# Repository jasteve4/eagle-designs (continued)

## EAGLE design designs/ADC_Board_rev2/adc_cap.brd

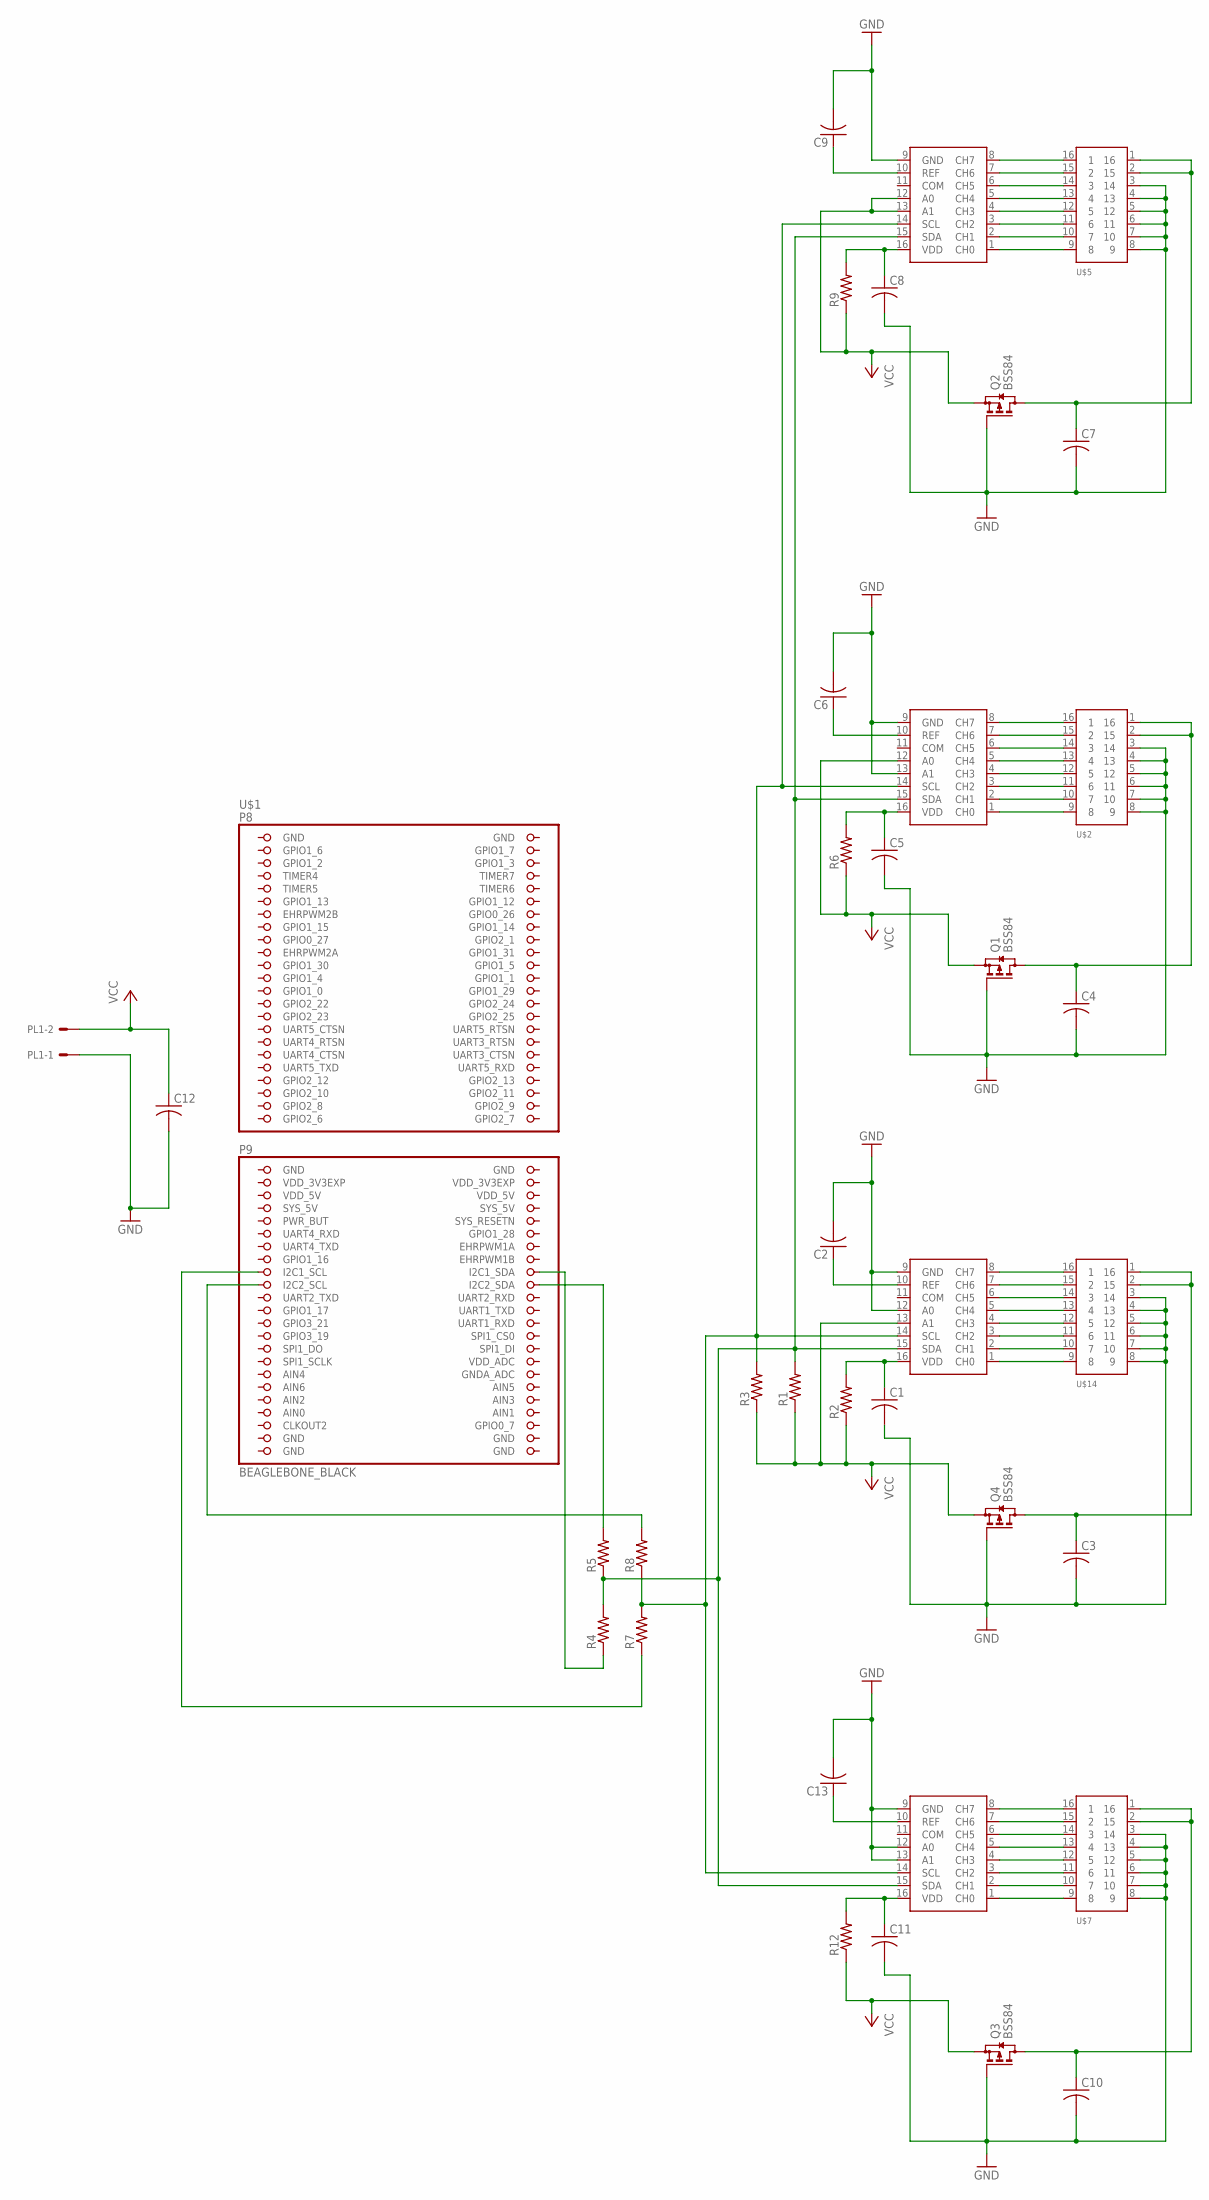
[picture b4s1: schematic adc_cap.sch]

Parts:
C1, C2, C3, C4, C5, C6, C7, C8, C9, C10, C11, C12, C13: C-USC0805; C0805
PL1: 555X-2H; 5569-2
Q1, Q2, Q3, Q4: BSS84; SOT23
R1, R2, R3, R4, R5, R6, R7, R8, R9, R12: R-US_R0805; R0805
U$1: BEAGLEBONE_BLACK; BEAGEBONE
U$2, U$5, U$7, U$14: 2_X_8_CON; 2_X_8_PIN
U$3, U$4, U$6, U$8: ADS7830; ADC8_SD

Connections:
AIN0: U$1.146 (AIN0)
GND: C1.2, C2.2, C3.2, C4.2, C5.2, C6.2, C7.2, C8.2, C9.2, C10.2, C11.2, C12.2, C13.2, PL1.1, Q1.1 (G), Q2.1 (G), Q3.1 (G), Q4.1 (G), U$1.137 (GND), U$1.138 (GND), U$1.139 (GND), U$1.140 (GND), U$1.141 (GND), U$1.142 (GND), U$1.183 (GND), U$1.184 (GND), U$2.3 (14), U$2.4 (13), U$2.5 (12), U$2.6 (11), U$2.7 (10), U$2.8 (9), U$3.9 (GND), U$3.12 (A0), U$4.9 (GND), U$4.13 (A1), U$5.3 (14), U$5.4 (13), U$5.5 (12), U$5.6 (11), U$5.7 (10), U$5.8 (9), U$6.9 (GND), U$7.3 (14), U$7.4 (13), U$7.5 (12), U$7.6 (11), U$7.7 (10), U$7.8 (9), U$8.9 (GND), U$8.12 (A0), U$8.13 (A1), U$14.3 (14), U$14.4 (13), U$14.5 (12), U$14.6 (11), U$14.7 (10), U$14.8 (9)
unnamed: U$3.1 (CH0), U$14.9 (8)
unnamed: R1.2, R4.2, R5.1, U$3.15 (SDA), U$4.15 (SDA), U$6.15 (SDA), U$8.15 (SDA)
unnamed: U$3.2 (CH1), U$14.10 (7)
unnamed: U$3.3 (CH2), U$14.11 (6)
unnamed: U$3.4 (CH3), U$14.12 (5)
unnamed: U$3.5 (CH4), U$14.13 (4)
unnamed: U$3.6 (CH5), U$14.14 (3)
unnamed: U$3.7 (CH6), U$14.15 (2)
unnamed: U$3.8 (CH7), U$14.16 (1)
unnamed: R5.2, U$1.167 (I2C2_SDA)
unnamed: C1.1, R2.2, U$3.16 (VDD)
unnamed: C2.1, U$3.10 (REF)
unnamed: R3.2, R7.2, R8.1, U$3.14 (SCL), U$4.14 (SCL), U$6.14 (SCL), U$8.14 (SCL)
unnamed: C4.1, Q1.3 (D), U$2.1 (16), U$2.2 (15)
unnamed: U$2.9 (8), U$4.1 (CH0)
unnamed: U$2.10 (7), U$4.2 (CH1)
unnamed: U$2.11 (6), U$4.3 (CH2)
unnamed: U$2.12 (5), U$4.4 (CH3)
unnamed: U$2.13 (4), U$4.5 (CH4)
unnamed: U$2.14 (3), U$4.6 (CH5)
unnamed: U$2.15 (2), U$4.7 (CH6)
unnamed: U$2.16 (1), U$4.8 (CH7)
unnamed: R4.1, U$1.165 (I2C1_SDA)
unnamed: R8.2, U$1.166 (I2C2_SCL)
unnamed: C5.1, R6.2, U$4.16 (VDD)
unnamed: C6.1, U$4.10 (REF)
unnamed: C7.1, Q2.3 (D), U$5.1 (16), U$5.2 (15)
unnamed: U$5.9 (8), U$6.1 (CH0)
unnamed: U$5.10 (7), U$6.2 (CH1)
unnamed: U$5.11 (6), U$6.3 (CH2)
unnamed: U$5.12 (5), U$6.4 (CH3)
unnamed: U$5.13 (4), U$6.5 (CH4)
unnamed: U$5.14 (3), U$6.6 (CH5)
unnamed: U$5.15 (2), U$6.7 (CH6)
unnamed: U$5.16 (1), U$6.8 (CH7)
unnamed: R7.1, U$1.168 (I2C1_SCL)
unnamed: C8.1, R9.2, U$6.16 (VDD)
unnamed: C9.1, U$6.10 (REF)
unnamed: C10.1, Q3.3 (D), U$7.1 (16), U$7.2 (15)
unnamed: U$7.9 (8), U$8.1 (CH0)
unnamed: U$7.10 (7), U$8.2 (CH1)
unnamed: U$7.11 (6), U$8.3 (CH2)
unnamed: U$7.12 (5), U$8.4 (CH3)
unnamed: U$7.13 (4), U$8.5 (CH4)
unnamed: U$7.14 (3), U$8.6 (CH5)
unnamed: U$7.15 (2), U$8.7 (CH6)
unnamed: U$7.16 (1), U$8.8 (CH7)
unnamed: C11.1, R12.2, U$8.16 (VDD)
unnamed: C13.1, U$8.10 (REF)
unnamed: C3.1, Q4.3 (D), U$14.1 (16), U$14.2 (15)
SYS_5V: U$1.178 (SYS_5V)
VCC: C12.1, PL1.2, Q1.2 (S), Q2.2 (S), Q3.2 (S), Q4.2 (S), R1.1, R2.1, R3.1, R6.1, R9.1, R12.1, U$3.13 (A1), U$4.12 (A0), U$6.12 (A0), U$6.13 (A1)
VDD_3V3EXP: U$1.181 (VDD_3V3EXP), U$1.182 (VDD_3V3EXP)
VDD_5V: U$1.179 (VDD_5V), U$1.180 (VDD_5V)

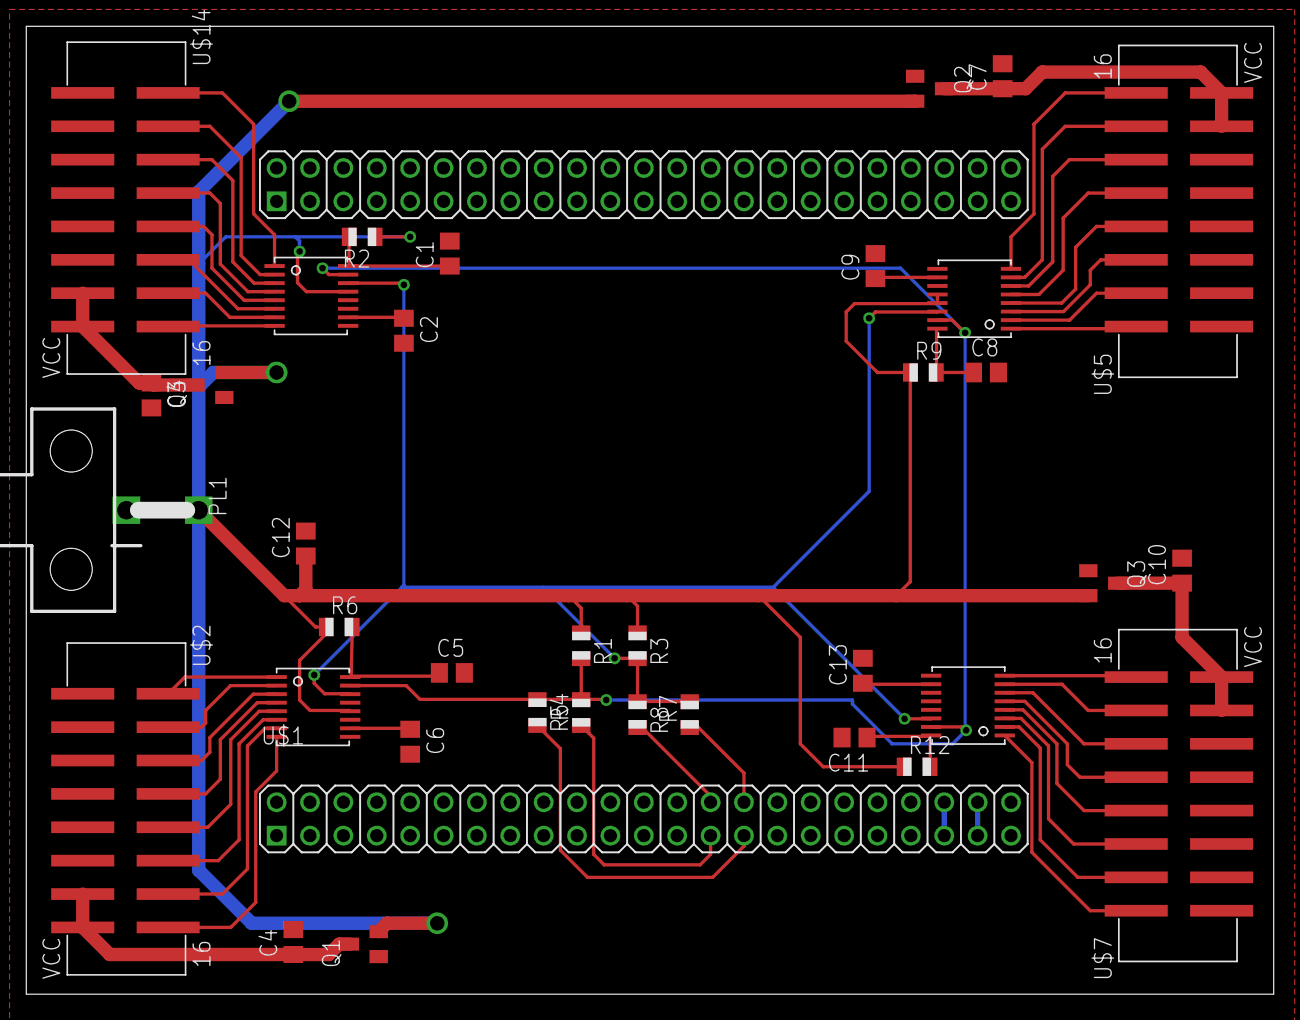
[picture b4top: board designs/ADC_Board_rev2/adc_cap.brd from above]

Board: 2 copper layers, 94.9 x 73.7 mm, 37 parts (0 on the bottom side), 54 nets.

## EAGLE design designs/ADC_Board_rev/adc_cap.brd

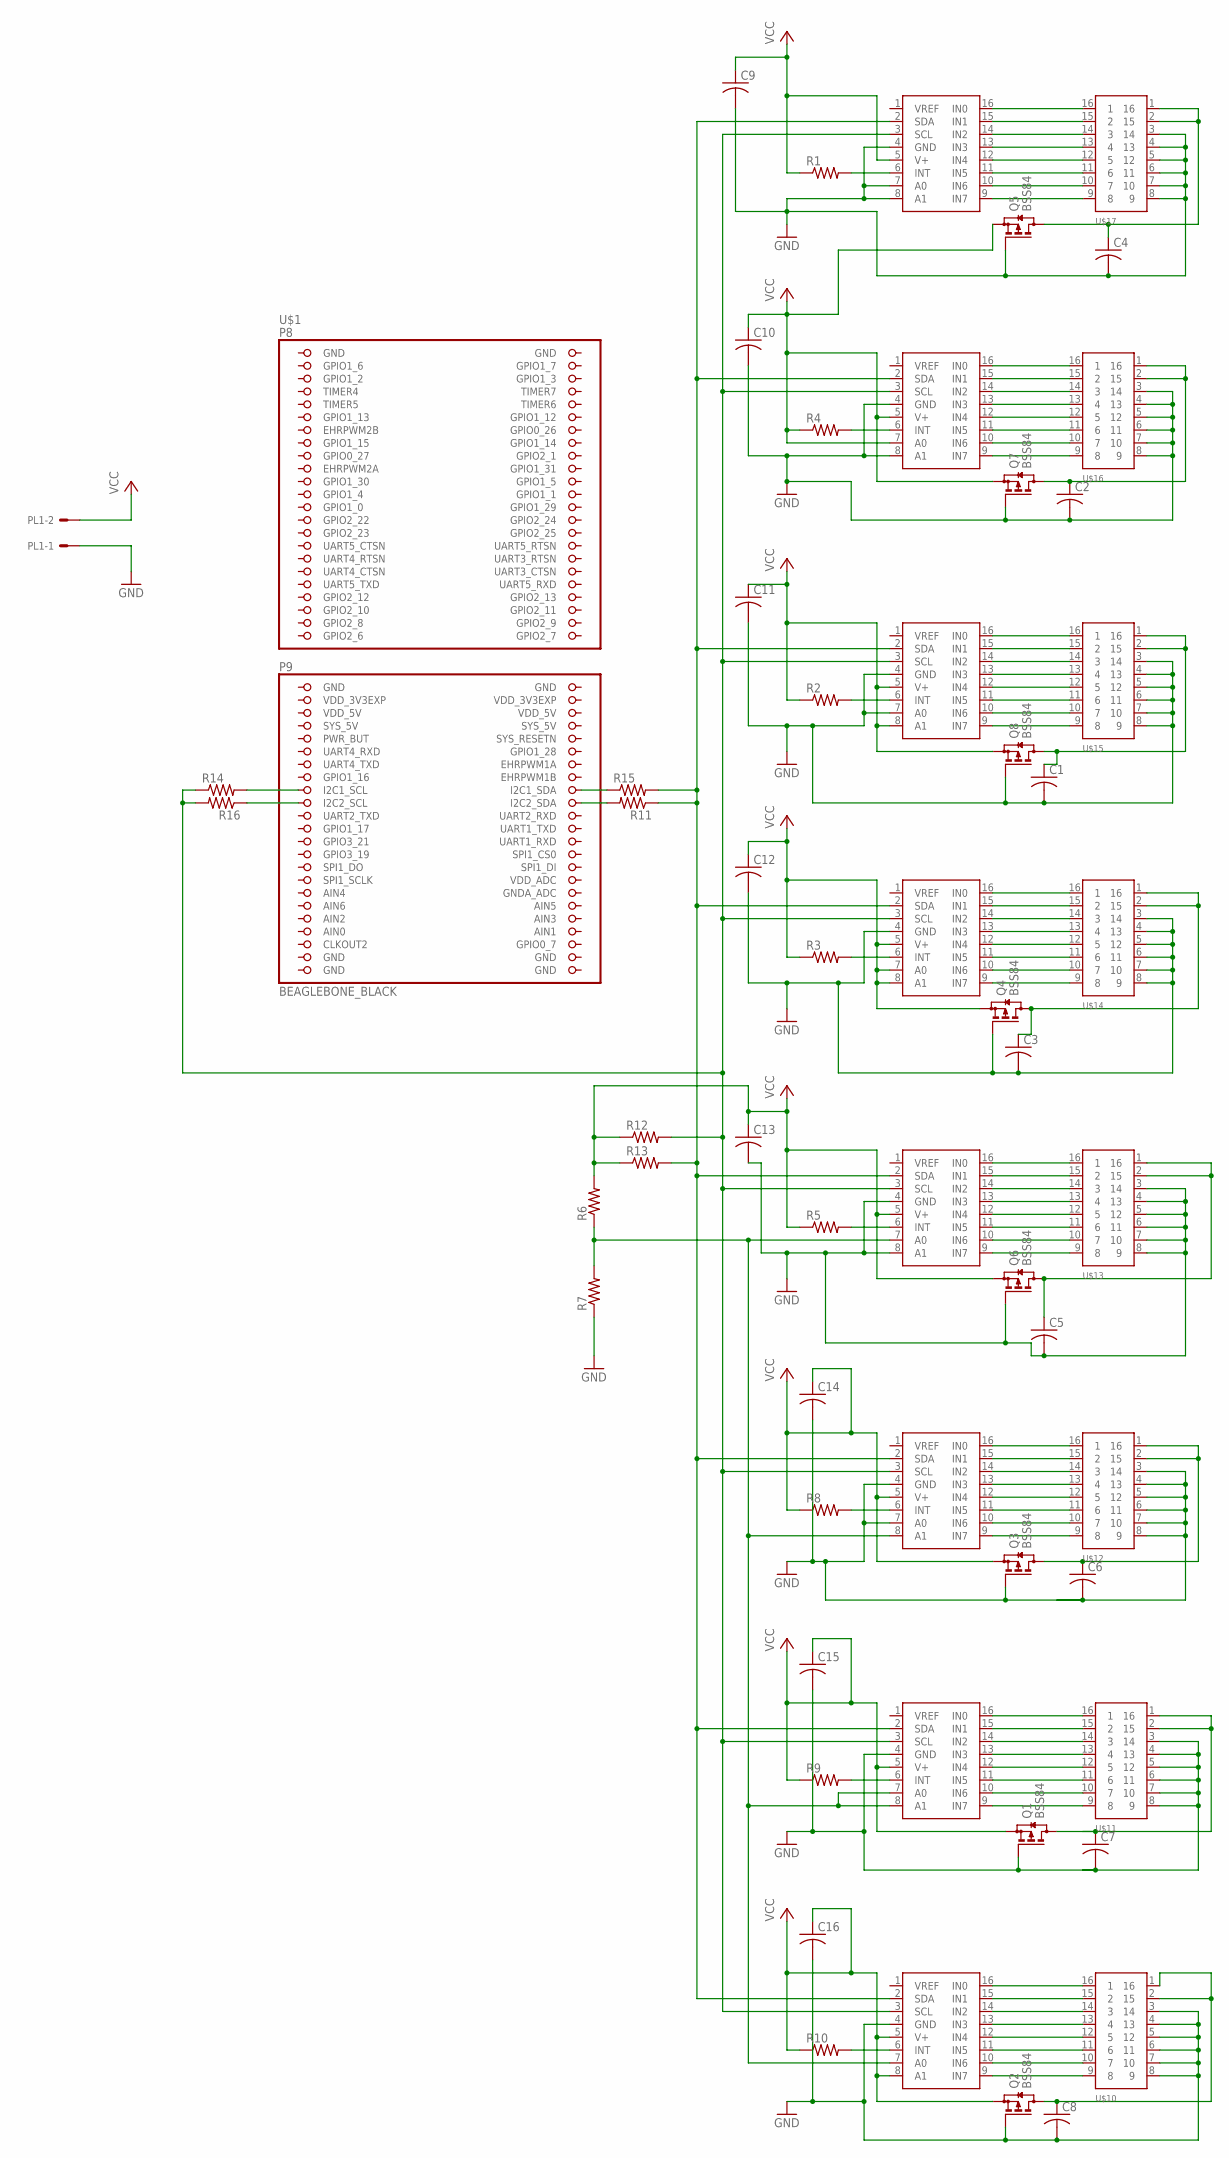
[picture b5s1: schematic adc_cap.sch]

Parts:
C1, C2, C3, C4, C5, C6, C7, C8, C9, C10, C11, C12, C13, C14, C15, C16: C-USC0805; C0805
PL1: 555X-2H; 5569-2
Q1, Q2, Q3, Q4, Q5, Q6, Q7, Q8: BSS84; SOT23
R1, R2, R3, R4, R5, R6, R7, R8, R9, R10, R11, R12, R13, R14, R15, R16: R-US_R0805; R0805
U$1: BEAGLEBONE_BLACK; BEAGEBONE
U$2, U$3, U$4, U$5, U$6, U$7, U$8, U$9: ADC128D818; ADC12_SD
U$10, U$11, U$12, U$13, U$14, U$15, U$16, U$17: 2_X_8_CON; 2_X_8_PIN

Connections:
AIN0: U$1.146 (AIN0)
GND: C1.2, C2.2, C3.2, C4.2, C5.2, C6.2, C7.2, C8.2, C9.2, C10.2, C11.2, C12.2, C13.2, C14.2, C15.2, C16.2, PL1.1, Q1.1 (G), Q2.1 (G), Q3.1 (G), Q4.1 (G), Q5.1 (G), Q6.1 (G), Q7.1 (G), Q8.1 (G), R7.1, U$1.137 (GND), U$1.138 (GND), U$1.139 (GND), U$1.140 (GND), U$1.141 (GND), U$1.142 (GND), U$1.183 (GND), U$1.184 (GND), U$2.4 (GND), U$2.8 (A1), U$3.4 (GND), U$3.7 (A0), U$3.8 (A1), U$4.4 (GND), U$4.7 (A0), U$5.4 (GND), U$6.4 (GND), U$6.8 (A1), U$7.4 (GND), U$7.7 (A0), U$8.4 (GND), U$9.4 (GND), U$10.3 (14), U$10.4 (13), U$10.5 (12), U$10.6 (11), U$10.7 (10), U$10.8 (9), U$11.3 (14), U$11.4 (13), U$11.5 (12), U$11.6 (11), U$11.7 (10), U$11.8 (9), U$12.3 (14), U$12.4 (13), U$12.5 (12), U$12.6 (11), U$12.7 (10), U$12.8 (9), U$13.3 (14), U$13.4 (13), U$13.5 (12), U$13.6 (11), U$13.7 (10), U$13.8 (9), U$14.3 (14), U$14.4 (13), U$14.5 (12), U$14.6 (11), U$14.7 (10), U$14.8 (9), U$15.3 (14), U$15.4 (13), U$15.5 (12), U$15.6 (11), U$15.7 (10), U$15.8 (9), U$16.3 (14), U$16.4 (13), U$16.5 (12), U$16.6 (11), U$16.7 (10), U$16.8 (9), U$17.3 (14), U$17.4 (13), U$17.5 (12), U$17.6 (11), U$17.7 (10), U$17.8 (9)
unnamed: U$3.16 (IN0), U$17.16 (1)
unnamed: U$3.15 (IN1), U$17.15 (2)
unnamed: U$3.14 (IN2), U$17.14 (3)
unnamed: U$3.13 (IN3), U$17.13 (4)
unnamed: U$3.12 (IN4), U$17.12 (5)
unnamed: U$3.11 (IN5), U$17.11 (6)
unnamed: U$3.10 (IN6), U$17.10 (7)
unnamed: U$3.9 (IN7), U$17.9 (8)
unnamed: U$9.16 (IN0), U$10.16 (1)
unnamed: U$9.15 (IN1), U$10.15 (2)
unnamed: U$9.14 (IN2), U$10.14 (3)
unnamed: U$9.13 (IN3), U$10.13 (4)
unnamed: U$9.12 (IN4), U$10.12 (5)
unnamed: U$9.11 (IN5), U$10.11 (6)
unnamed: U$9.10 (IN6), U$10.10 (7)
unnamed: U$9.9 (IN7), U$10.9 (8)
unnamed: U$8.16 (IN0), U$11.16 (1)
unnamed: U$8.15 (IN1), U$11.15 (2)
unnamed: R4.2, U$2.6 (INT)
unnamed: U$8.14 (IN2), U$11.14 (3)
unnamed: U$8.13 (IN3), U$11.13 (4)
unnamed: U$8.12 (IN4), U$11.12 (5)
unnamed: U$8.11 (IN5), U$11.11 (6)
unnamed: U$8.10 (IN6), U$11.10 (7)
unnamed: U$8.9 (IN7), U$11.9 (8)
unnamed: R2.2, U$4.6 (INT)
unnamed: U$7.16 (IN0), U$12.16 (1)
unnamed: U$7.15 (IN1), U$12.15 (2)
unnamed: U$7.14 (IN2), U$12.14 (3)
unnamed: U$7.13 (IN3), U$12.13 (4)
unnamed: U$7.12 (IN4), U$12.12 (5)
unnamed: U$7.11 (IN5), U$12.11 (6)
unnamed: U$7.10 (IN6), U$12.10 (7)
unnamed: U$7.9 (IN7), U$12.9 (8)
unnamed: R3.2, U$5.6 (INT)
unnamed: U$6.16 (IN0), U$13.16 (1)
unnamed: U$6.15 (IN1), U$13.15 (2)
unnamed: U$6.14 (IN2), U$13.14 (3)
unnamed: U$6.13 (IN3), U$13.13 (4)
unnamed: U$6.12 (IN4), U$13.12 (5)
unnamed: U$6.11 (IN5), U$13.11 (6)
unnamed: U$6.10 (IN6), U$13.10 (7)
unnamed: U$6.9 (IN7), U$13.9 (8)
unnamed: R5.2, U$6.6 (INT)
unnamed: R6.1, R7.2, U$6.7 (A0), U$7.8 (A1), U$8.7 (A0), U$8.8 (A1), U$9.7 (A0)
unnamed: U$5.16 (IN0), U$14.16 (1)
unnamed: U$5.15 (IN1), U$14.15 (2)
unnamed: U$5.14 (IN2), U$14.14 (3)
unnamed: U$5.13 (IN3), U$14.13 (4)
unnamed: U$5.12 (IN4), U$14.12 (5)
unnamed: U$5.11 (IN5), U$14.11 (6)
unnamed: U$5.10 (IN6), U$14.10 (7)
unnamed: U$5.9 (IN7), U$14.9 (8)
unnamed: R8.2, U$7.6 (INT)
unnamed: R12.2, R14.1, R16.2, U$2.3 (SCL), U$3.3 (SCL), U$4.3 (SCL), U$5.3 (SCL), U$6.3 (SCL), U$7.3 (SCL), U$8.3 (SCL), U$9.3 (SCL)
unnamed: U$4.16 (IN0), U$15.16 (1)
unnamed: U$4.15 (IN1), U$15.15 (2)
unnamed: U$4.14 (IN2), U$15.14 (3)
unnamed: U$4.13 (IN3), U$15.13 (4)
unnamed: U$4.12 (IN4), U$15.12 (5)
unnamed: U$4.11 (IN5), U$15.11 (6)
unnamed: U$4.10 (IN6), U$15.10 (7)
unnamed: U$4.9 (IN7), U$15.9 (8)
unnamed: R9.2, U$8.6 (INT)
unnamed: U$2.16 (IN0), U$16.16 (1)
unnamed: U$2.15 (IN1), U$16.15 (2)
unnamed: R1.2, U$3.6 (INT)
unnamed: U$2.14 (IN2), U$16.14 (3)
unnamed: U$2.13 (IN3), U$16.13 (4)
unnamed: U$2.12 (IN4), U$16.12 (5)
unnamed: U$2.11 (IN5), U$16.11 (6)
unnamed: U$2.10 (IN6), U$16.10 (7)
unnamed: U$2.9 (IN7), U$16.9 (8)
unnamed: R10.2, U$9.6 (INT)
unnamed: C4.1, Q5.3 (D), U$17.1 (16), U$17.2 (15)
unnamed: C3.1, Q4.3 (D), U$14.1 (16), U$14.2 (15)
unnamed: C1.1, Q8.3 (D), U$15.1 (16), U$15.2 (15)
unnamed: C7.1, Q1.3 (D), U$11.1 (16), U$11.2 (15)
unnamed: C2.1, Q7.3 (D), U$16.1 (16), U$16.2 (15)
unnamed: R11.2, U$1.167 (I2C2_SDA)
unnamed: R15.1, U$1.165 (I2C1_SDA)
unnamed: C5.1, Q6.3 (D), U$13.1 (16), U$13.2 (15)
unnamed: C8.1, Q2.3 (D), U$10.1 (16), U$10.2 (15)
unnamed: R11.1, R13.2, R15.2, U$2.2 (SDA), U$3.2 (SDA), U$4.2 (SDA), U$5.2 (SDA), U$6.2 (SDA), U$7.2 (SDA), U$8.2 (SDA), U$9.2 (SDA)
unnamed: R14.2, U$1.168 (I2C1_SCL)
unnamed: R16.1, U$1.166 (I2C2_SCL)
unnamed: C6.1, Q3.3 (D), U$12.1 (16), U$12.2 (15)
SYS_5V: U$1.178 (SYS_5V)
VCC: C9.1, C10.1, C11.1, C12.1, C13.1, C14.1, C15.1, C16.1, PL1.2, Q1.2 (S), Q2.2 (S), Q3.2 (S), Q4.2 (S), Q5.2 (S), Q6.2 (S), Q7.2 (S), Q8.2 (S), R1.1, R2.1, R3.1, R4.1, R5.1, R6.2, R8.1, R9.1, R10.1, R12.1, R13.1, U$2.5 (V+), U$2.7 (A0), U$3.5 (V+), U$4.5 (V+), U$4.8 (A1), U$5.5 (V+), U$5.7 (A0), U$5.8 (A1), U$6.5 (V+), U$7.5 (V+), U$8.5 (V+), U$9.5 (V+), U$9.8 (A1)
VDD_3V3EXP: U$1.181 (VDD_3V3EXP), U$1.182 (VDD_3V3EXP)
VDD_5V: U$1.179 (VDD_5V), U$1.180 (VDD_5V)

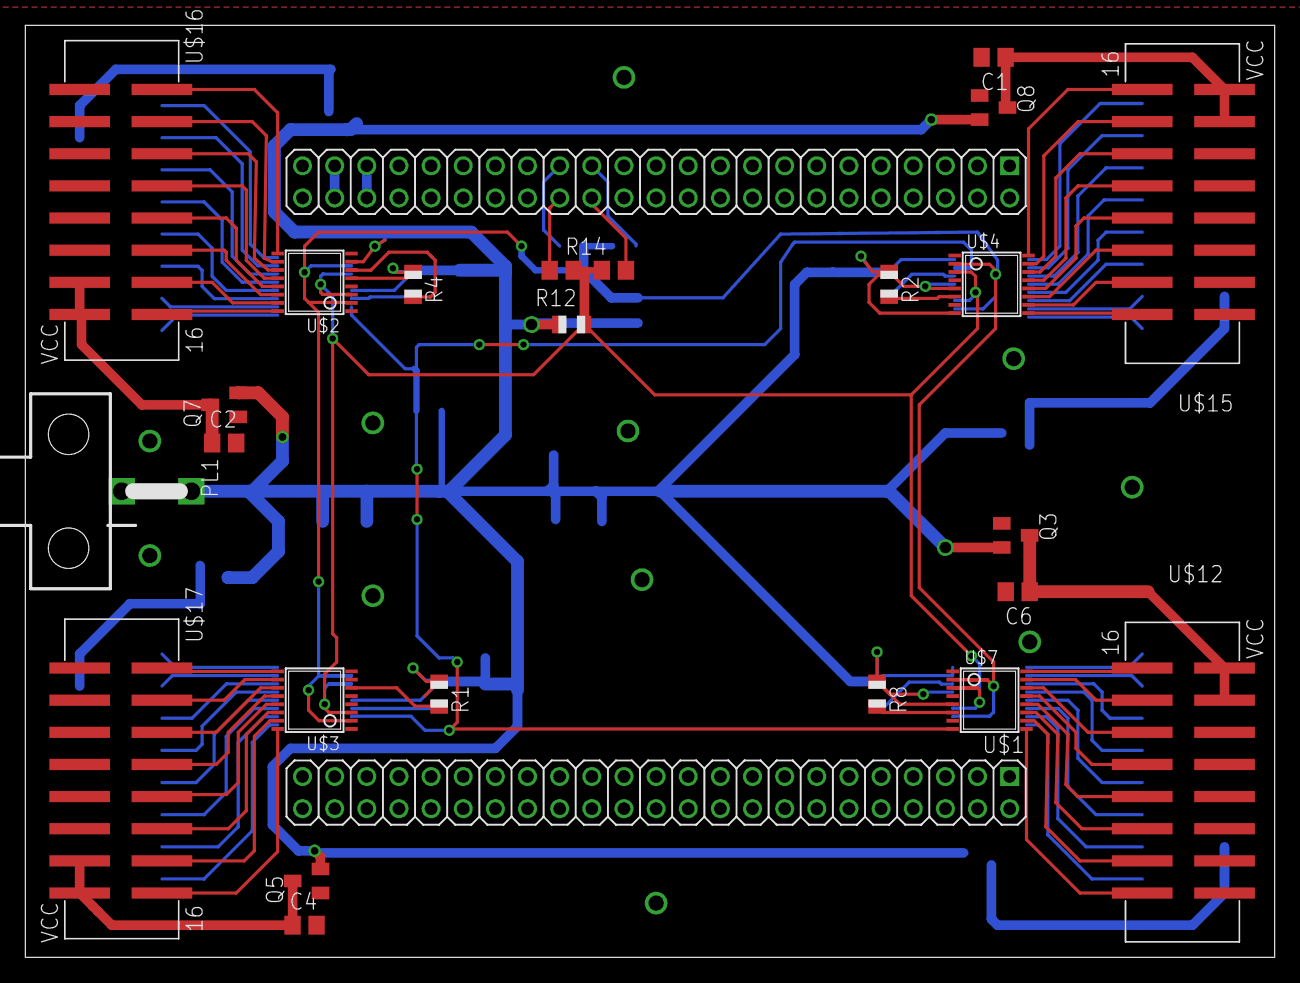
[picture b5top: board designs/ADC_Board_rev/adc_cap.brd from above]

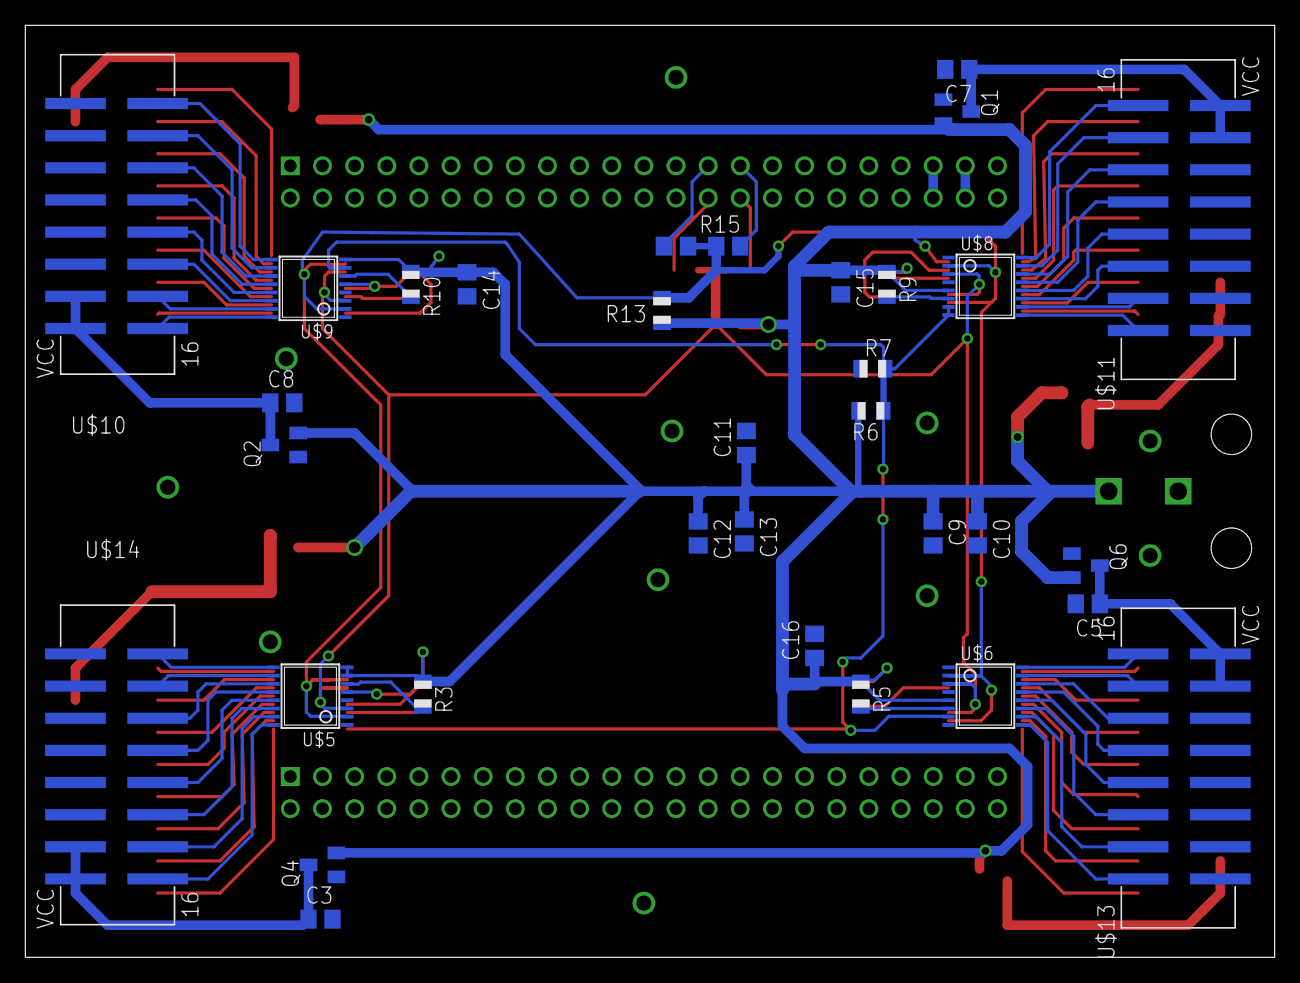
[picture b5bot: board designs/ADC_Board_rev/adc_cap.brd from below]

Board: 2 copper layers, 98.7 x 73.7 mm, 58 parts (33 on the bottom side), 91 nets.

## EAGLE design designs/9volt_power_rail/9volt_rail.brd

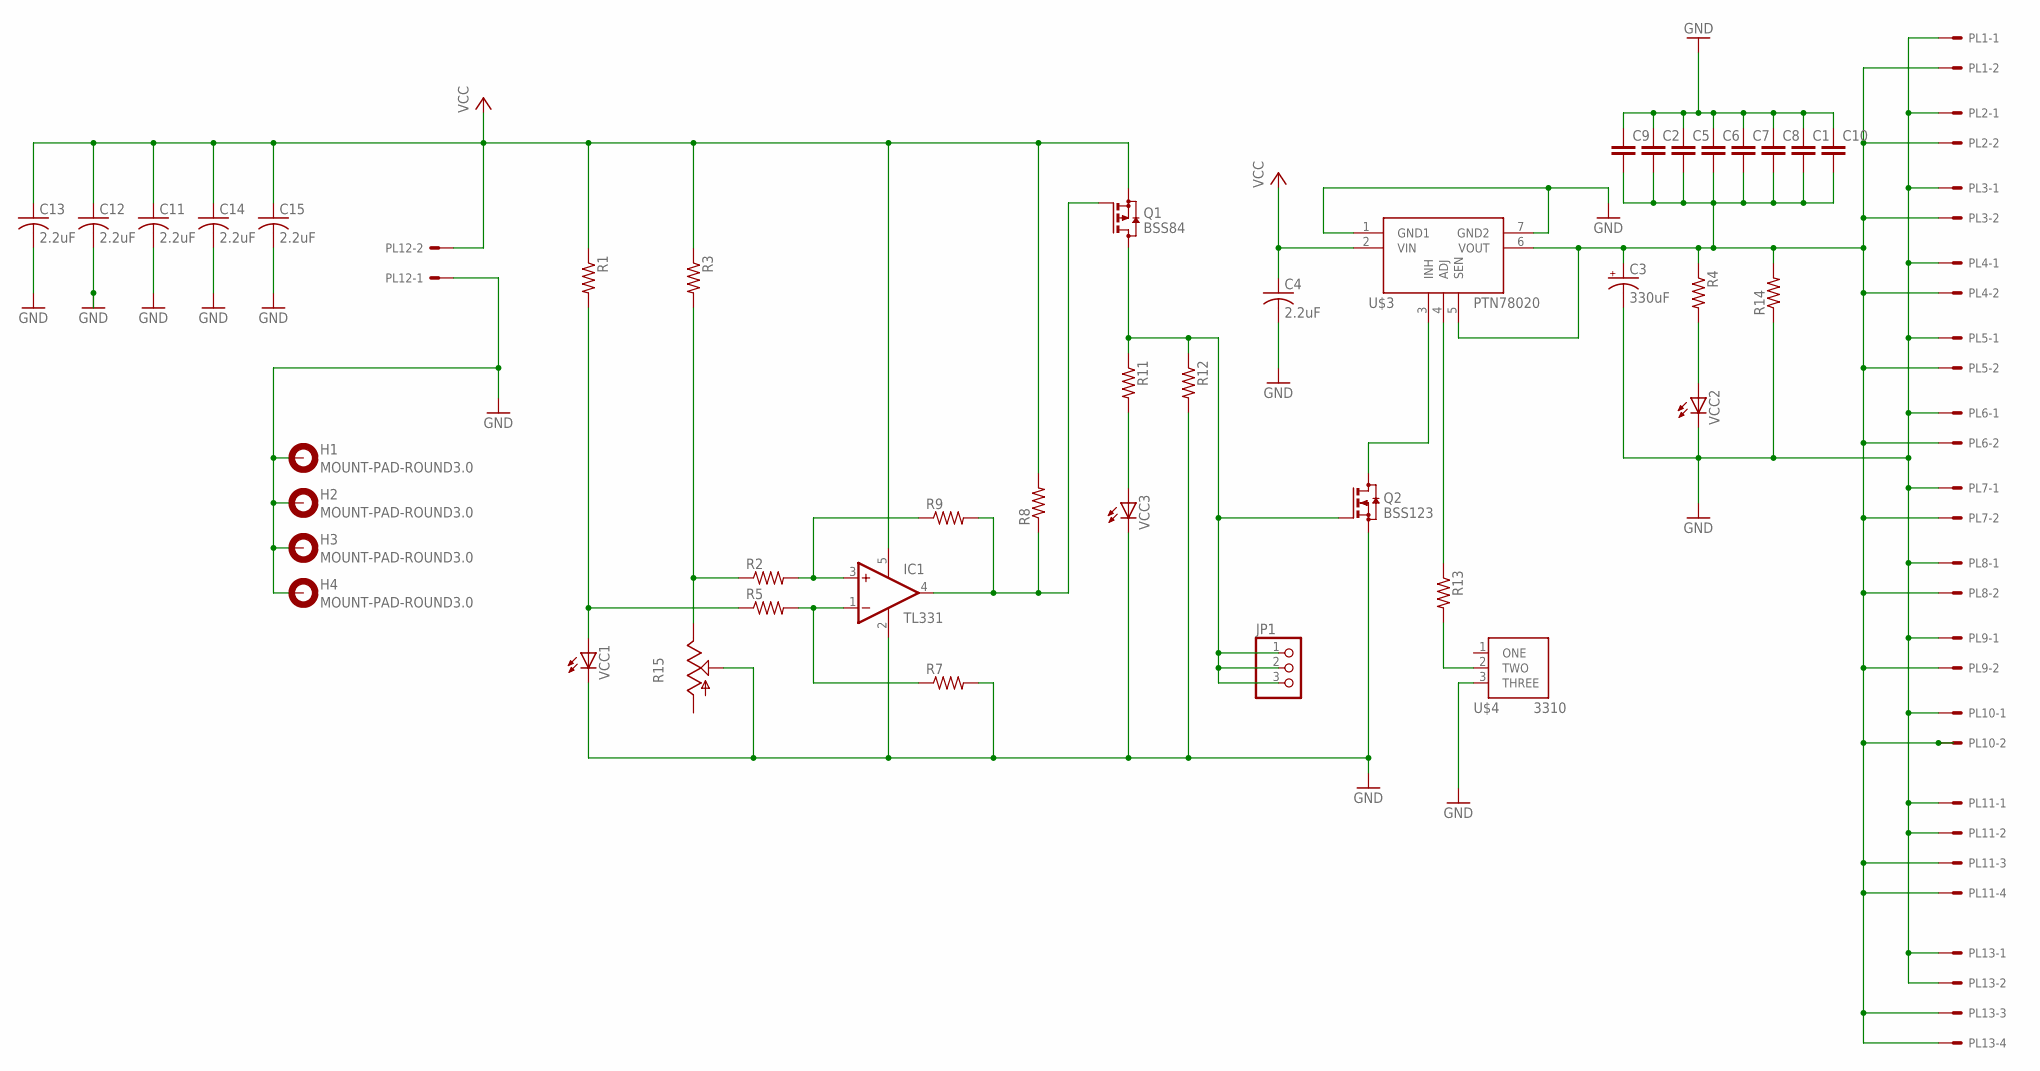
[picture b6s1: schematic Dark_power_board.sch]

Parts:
C1, C2, C5, C6, C7, C8, C9, C10: C-EUC0805; C0805
C3: 330uF; E5-10,5
C4, C11, C12, C13, C14, C15: 2.2uF; C0805
H1, H2, H3, H4: MOUNT-PAD-ROUND3.0; 3,0-PAD
IC1: TL331; DBV-R-PDSO-G5
JP1: PINHD-1X3; 1X03
PL1, PL2, PL3, PL4, PL5, PL6, PL7, PL8, PL9, PL10, PL12: 555X-2H; 5569-2
PL11, PL13: 555X-4H; 5569-4
Q1: BSS84; SOT23
Q2: BSS123; SOT23
R1, R2, R3, R4, R5, R7, R8, R9, R11, R12, R13: R-US_M0805; M0805
R14: R-US_0617/17; 0617/17
R15: TRIM_US-S63P; S63P
U$3: PTH78020-SMD; PTN78020-SND
U$4: 3310-001; 3310-001-TH
VCC1, VCC2, VCC3: LED5MM

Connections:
GND: C1.1, C2.1, C3.-, C4.2, C5.1, C6.1, C7.1, C8.1, C9.1, C10.1, C11.2, C12.2, C13.2, C14.2, C15.2, H1.B3,0, H2.B3,0, H3.B3,0, H4.B3,0, IC1.2 (GND), PL1.1, PL2.1, PL3.1, PL4.1, PL5.1, PL6.1, PL7.1, PL8.1, PL9.1, PL10.1, PL11.1, PL11.2, PL12.1, PL13.1, PL13.2, Q2.2 (S), R7.2, R12.2, R14.1, R15.S, U$3.1 (GND1), U$3.7 (GND2), U$4.3 (THREE), VCC1.K (C), VCC2.K (C), VCC3.K (C)
unnamed: R13.2, U$4.2 (TWO)
unnamed: IC1.4 (OUT), Q1.1 (G), R8.1, R9.2
unnamed: R1.2, R5.1, VCC1.A
unnamed: IC1.3 (+IN), R2.2, R9.1
unnamed: JP1.1, JP1.2, JP1.3, Q1.3 (D), Q2.1 (G), R11.1, R12.1
unnamed: R2.1, R3.2, R15.E
unnamed: IC1.1 (-IN), R5.2, R7.1
unnamed: R11.2, VCC3.A
unnamed: R4.2, VCC2.A
unnamed: Q2.3 (D), U$3.3 (INH)
unnamed: C1.2, C2.2, C3.+, C5.2, C6.2, C7.2, C8.2, C9.2, C10.2, PL1.2, PL2.2, PL3.2, PL4.2, PL5.2, PL6.2, PL7.2, PL8.2, PL9.2, PL10.2, PL11.3, PL11.4, PL13.3, PL13.4, R4.1, R14.2, U$3.5 (SEN), U$3.6 (VOUT)
unnamed: R13.1, U$3.4 (ADJ)
VCC: C4.1, C11.1, C12.1, C13.1, C14.1, C15.1, IC1.5 (V+), PL12.2, Q1.2 (S), R1.1, R3.1, R8.2, U$3.2 (VIN)

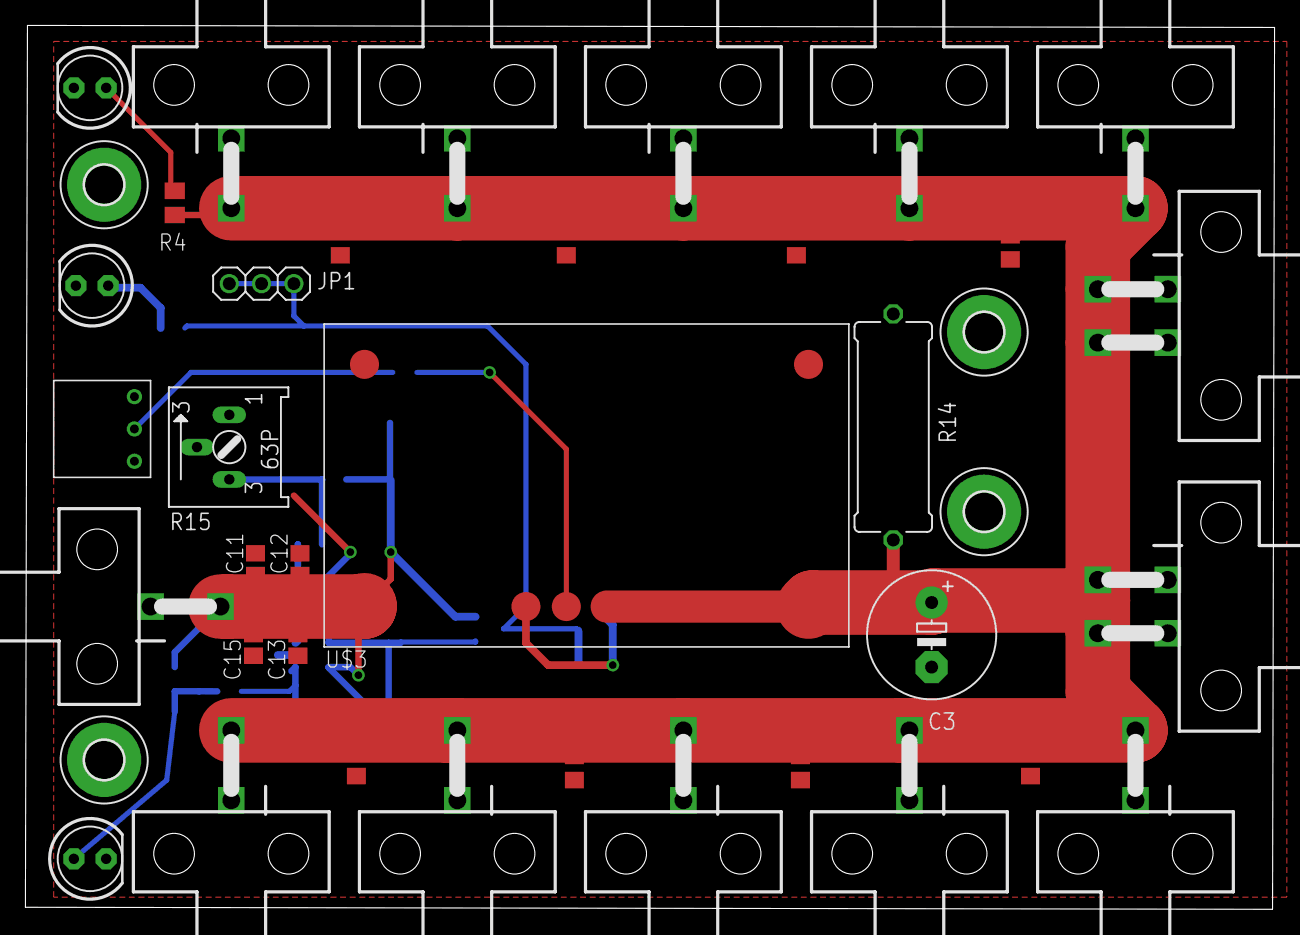
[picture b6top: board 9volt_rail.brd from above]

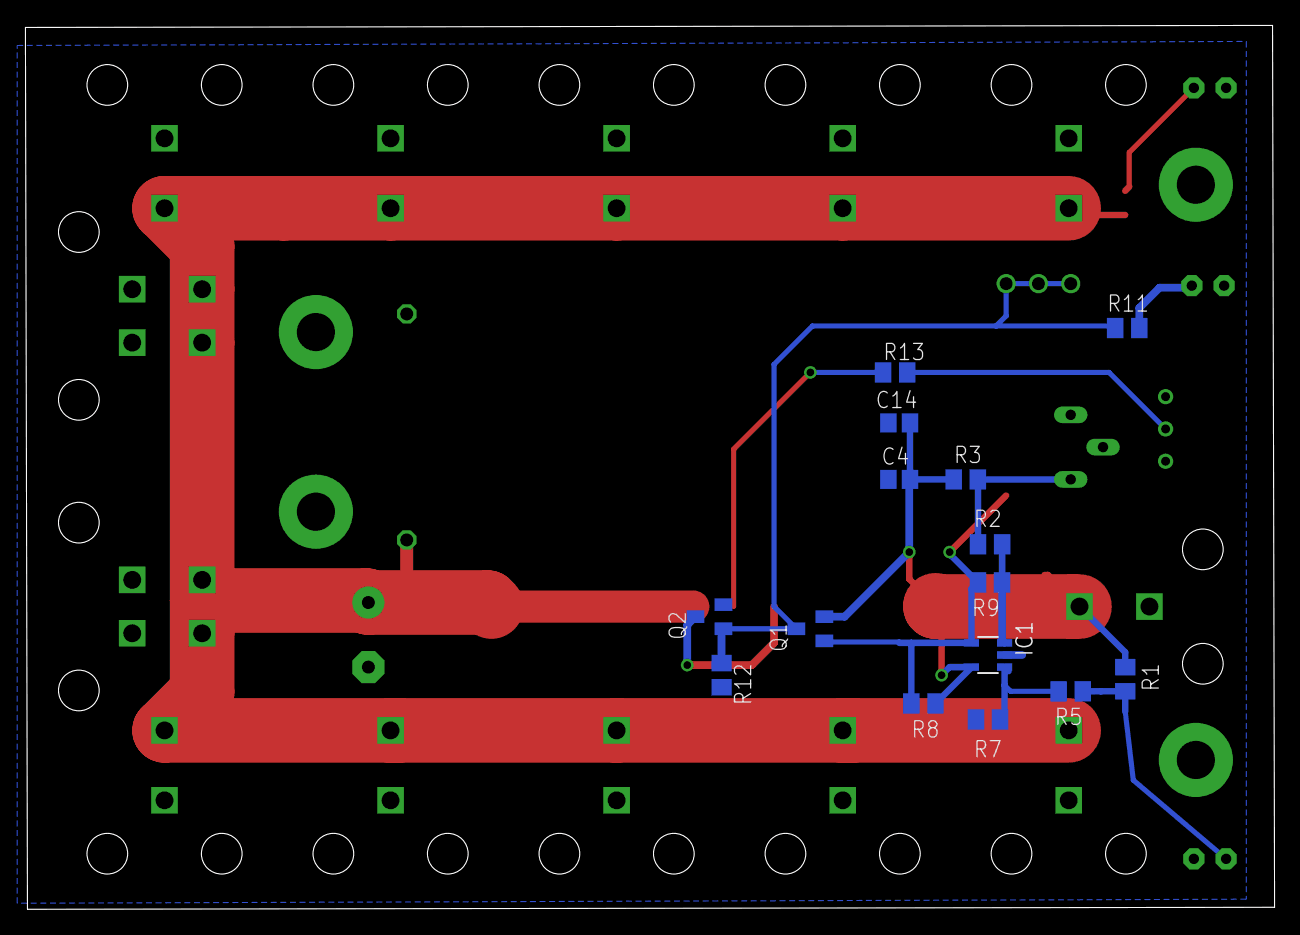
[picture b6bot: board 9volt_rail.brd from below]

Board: 2 copper layers, 98.3 x 69.5 mm, 54 parts (15 on the bottom side), 14 nets.

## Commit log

2015-01-11 Adding all files for IEEE Roobicts
2015-01-11 add the cam file
2015-01-11 Changed File name to make more sence
2015-01-12 Adding the power board
2015-01-12 Add Ti lib to project
2015-01-13 Initil file for rev 3
2015-01-14 Add files for Advanced circuits
2015-01-14 Update on adc rev 3
2015-01-15 Done with ADC cap rev 3
2015-01-27 update to to adc rev 3
2015-01-27 done with adc rev3
2015-01-27 update to adc_cap rev3
